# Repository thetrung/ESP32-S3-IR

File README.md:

# ESP32-S3 IR Sensor 
Just an ESP32-S3 with IR Sensor, some buttons for modes, OLED 128x32 to show info.

### 1. Layout

### 2. Schematic

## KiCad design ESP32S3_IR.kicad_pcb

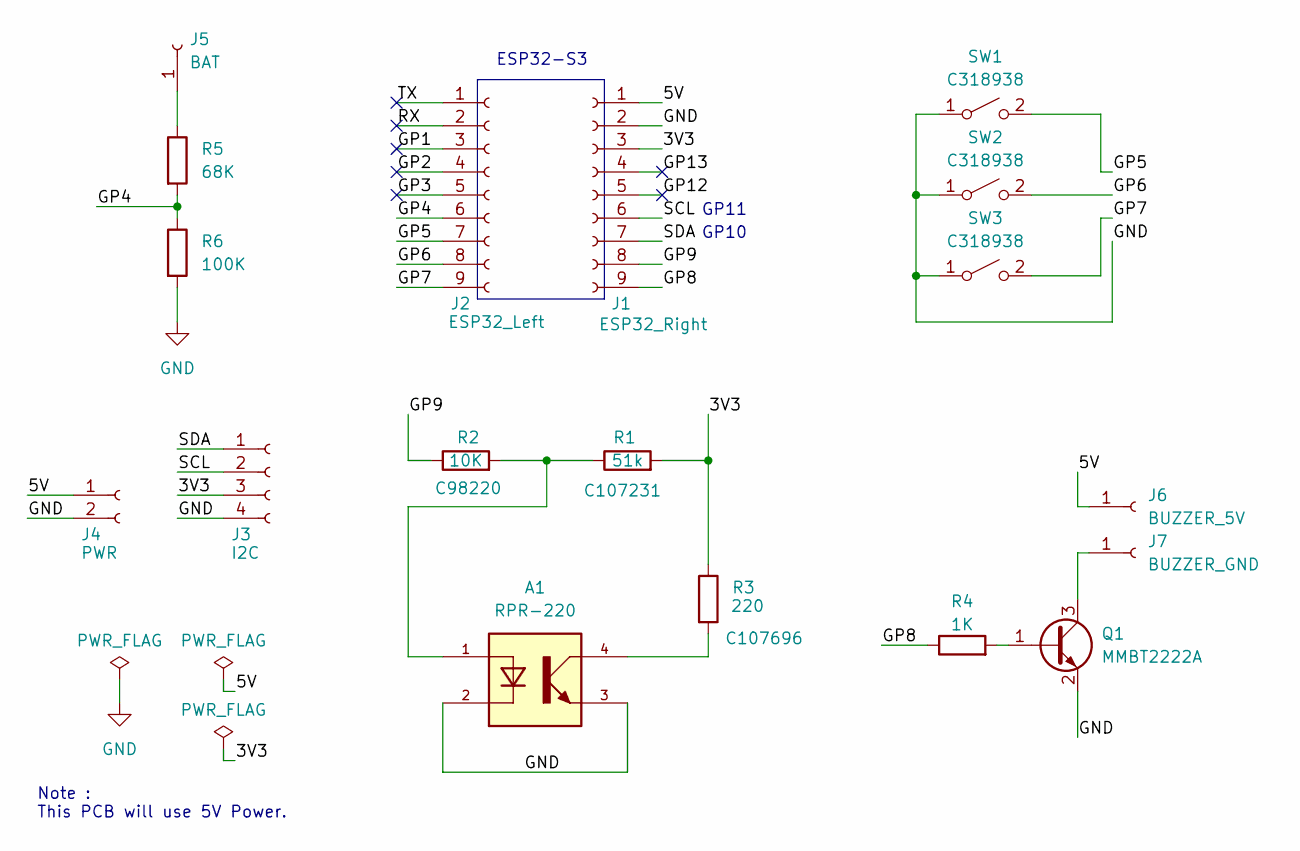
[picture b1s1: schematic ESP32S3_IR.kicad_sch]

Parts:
A1: RPR-220; PHODET_RPR-220; PARTREV B
J1: ESP32_Right; PinHeader_1x09_P2.54mm_Vertical
J2: ESP32_Left; PinHeader_1x09_P2.54mm_Vertical
J3: I2C; PinSocket_1x04_P2.54mm_Vertical
J4: PWR; PinSocket_1x02_P2.54mm_Vertical
J5: BAT; PinSocket_1x01_P2.54mm_Vertical
J6: BUZZER_5V; PinSocket_1x01_P2.54mm_Vertical
J7: BUZZER_GND; PinSocket_1x01_P2.54mm_Vertical
Q1: MMBT2222A; SOT-23
R1: C107231; R_0603_1608Metric
R2: C98220; R_0603_1608Metric
R3: C107696; R_0603_1608Metric
R4: 1K; R_0603_1608Metric
R5: 68K; R_0603_1608Metric
R6: 100K; R_0603_1608Metric
SW1, SW2, SW3: C318938; SW_PUSH_6mm

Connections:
/3V3: J1.3, J3.3, R1.2, R3.1
/5V: J1.1, J4.1, J6.1
/GP1: J2.3
/GP2: J2.4
/GP3: J2.5
/GP4: J2.6, R5.2, R6.1
/GP5: J2.7, SW1.2 (B)
/GP6: J2.8, SW2.2 (B)
/GP7: J2.9, SW3.2 (B)
/GP8: J1.9, R4.1
/GP9: J1.8, R2.1
/GP12: J1.5
/GP13: J1.4
/RX: J2.2
/SCL: J1.6, J3.2
/SDA: J1.7, J3.1
/TX: J2.1
GND: A1.2, A1.3, J1.2, J3.4, J4.2, Q1.2 (E), R6.2, SW1.1 (A), SW2.1 (A), SW3.1 (A)
unnamed: A1.1, R1.1, R2.2
unnamed: A1.4, R3.2
unnamed: J5.1, R5.1
unnamed: J7.1, Q1.3 (C)
unnamed: Q1.1 (B), R4.2

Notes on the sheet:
ESP32-S3
Note : This PCB will use 5V Power.
GP10
GP11

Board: 2 copper layers, 18 parts (11 on the bottom side), 16 nets, no tracks yet.

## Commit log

2025-05-22 init Schematic + Layout
2025-05-22 update layout: change OLED placement
2025-05-22 Flip all except ESP32 -> B.Cu
2025-06-03 update buzzer->5V
2025-06-04 update SCH: add battery sensor ADC & split net into 3V3 & 5V powerline.
2025-06-04 change ADC sensor pin 3V3 -> BAT socket
2025-06-11 Change Layout-> Fit Early THT requirement
